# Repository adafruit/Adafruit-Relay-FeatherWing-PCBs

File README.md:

## Adafruit Relay FeatherWing PCBs
&nbsp; <br />
Click to purchase from the Adafruit Shop:
- [Latching Mini Relay FeatherWing](https://www.adafruit.com/product/2923)
- [Non-Latching Mini Relay FeatherWing](https://www.adafruit.com/product/2895)

The are two 'flavors' of these FeatherWings, one is the Latching relay, requires two pins, a SET and UNSET and instead of keeping the SET pin high, you only have to pulse each pin high for 10ms to latch the relay open or closed. You need two pins but save power. Note, if power is lost, the relay will stay in the last setting.

The other type of relay FeatherWing is the simple Non-Latching relay, it requires only a single signal pin.

Both FeatherWings use the same family of relay. You can switch up to 2A of resistive current at 30VDC or ~40VAC or lower. At 110VDC you can switch up to 0.3A, at 120VAC up to 0.5A, and at 250VAC you can switch up to 0.6A. Check the datasheet for the relay for the exact switching capacity, and of course, for reactive/inductive loads you will need to derate. This isn't a relay you can use to turn on and off your washer/dryer, stick to 60W or less. For up to 1200W devices, check out our Power Featherwing which can handle up to 10A!

For more details, check out the product pages at
- https://www.adafruit.com/products/2923
- https://www.adafruit.com/products/2895

This is the PCB files for the Adafruit Relay FeatherWings. The format is EagleCAD schematic and board layout

### License

Adafruit invests time and resources providing this open source design, please support Adafruit and open-source hardware by purchasing products from [Adafruit](https://www.adafruit.com)!

All text above must be included in any redistribution

Designed by Limor Fried/Ladyada for Adafruit Industries.
Creative Commons Attribution/Share-Alike, all text above must be included in any redistribution. 
See license.txt for additional information.

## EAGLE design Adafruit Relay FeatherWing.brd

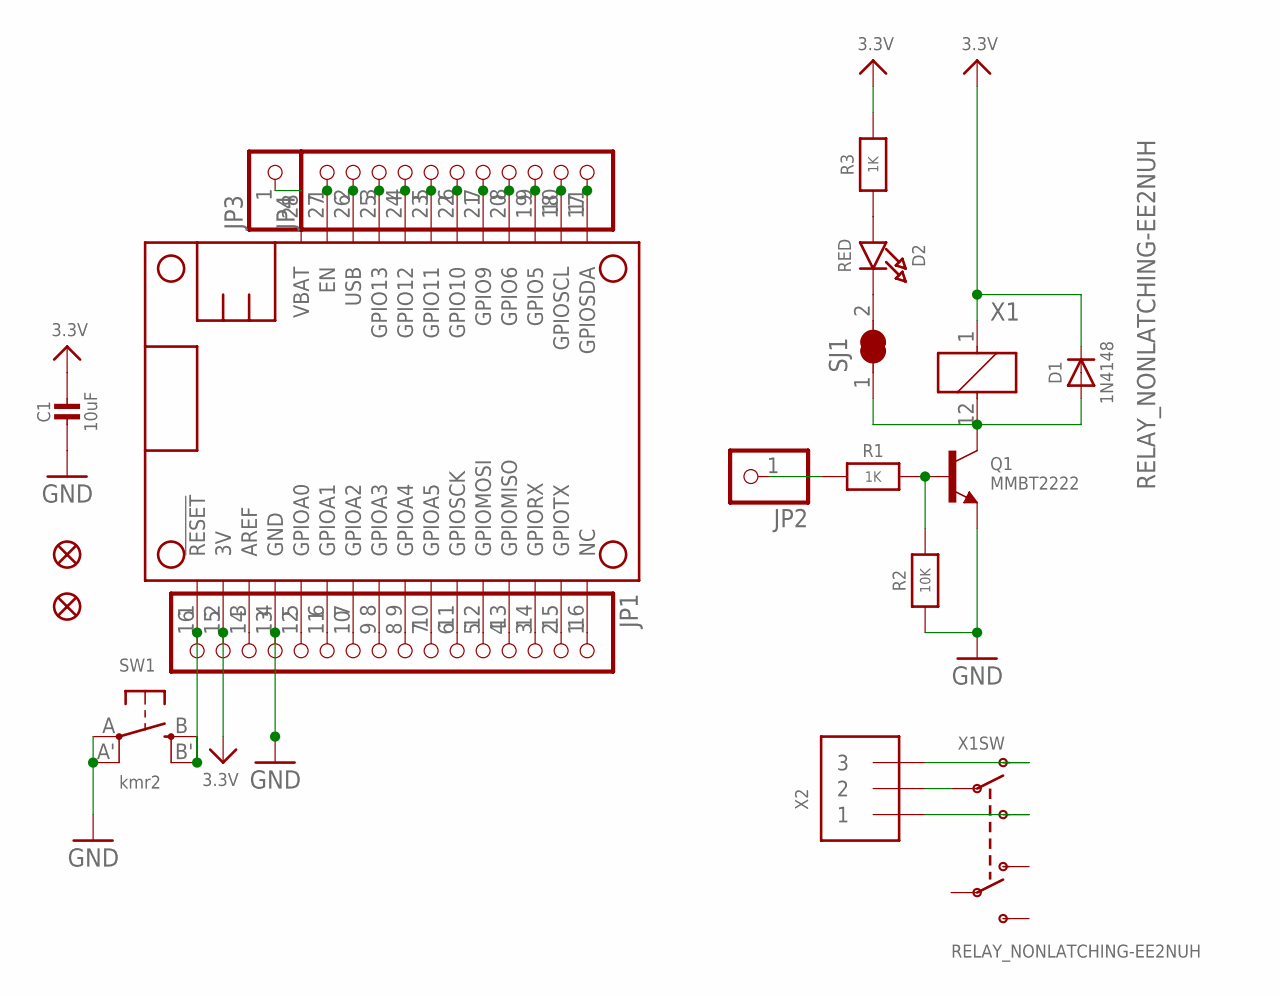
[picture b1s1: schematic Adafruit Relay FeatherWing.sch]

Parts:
C1: 10uF; 0805-NO
D1: 1N4148; SOD-323
D2: RED; CHIPLED_0805_NOOUTLINE
FID2, FID3: FIDUCIAL""; FIDUCIAL_1MM
JP1: HEADER-1X16ROUND; 1X16_ROUND
JP2, JP3: HEADER-1X1ROUND; 1X01_ROUND
JP4: HEADER-1X11; 1X11_ROUND
MS1: MICROSHIELD
Q1: MMBT2222; SOT23-R
R1, R3: 1K; 0805-NO
R2: 10K; 0805-NO
SJ1: SOLDERJUMPER_CLOSED; SOLDERJUMPER_CLOSEDWIRE
SW1: kmr2; BTN_KMR2_4.6X2.8
X1: RELAY_NONLATCHING-EE2NUH; RELAY_EE2_NOLATCH
X2: TERMBLOCK_1X3; TERMBLOCK_1X3-3.5MM

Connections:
3.3V: C1.1, D1.C, JP1.15, MS1.2 (3V), R3.2, X1.1
COM1: X1.9 (P1), X2.2
GND: C1.2, JP1.13, MS1.4 (GND), Q1.2 (E), R2.1, SW1.A, SW1.A' (P1)
unnamed: D1.A, Q1.3 (C), SJ1.1, X1.12 (2)
unnamed: JP1.1, MS1.16 (NC)
unnamed: JP1.2, MS1.15 (GPIOTX)
unnamed: JP1.3, MS1.14 (GPIORX)
unnamed: JP1.4, MS1.13 (GPIOMISO)
unnamed: JP1.5, MS1.12 (GPIOMOSI)
unnamed: JP1.6, MS1.11 (GPIOSCK)
unnamed: JP1.7, MS1.10 (GPIOA5)
unnamed: JP1.8, MS1.9 (GPIOA4)
unnamed: JP1.9, MS1.8 (GPIOA3)
unnamed: JP1.10, MS1.7 (GPIOA2)
unnamed: JP1.11, MS1.6 (GPIOA1)
unnamed: JP1.12, MS1.5 (GPIOA0)
unnamed: JP4.1, MS1.27 (EN)
unnamed: JP4.3, MS1.25 (GPIO13)
unnamed: JP4.4, MS1.24 (GPIO12)
unnamed: JP4.5, MS1.23 (GPIO11)
unnamed: JP4.6, MS1.22 (GPIO10)
unnamed: JP4.7, MS1.21 (GPIO9)
unnamed: JP4.8, MS1.20 (GPIO6)
unnamed: JP4.9, MS1.19 (GPIO5)
unnamed: Q1.1 (B), R1.2, R2.2
unnamed: JP1.14, MS1.3 (AREF)
unnamed: JP2.1, R1.1
unnamed: D2.C, SJ1.2
unnamed: D2.A, R3.1
unnamed: X1.10 (O1), X2.3
NO1: X1.8 (S1), X2.1
RESET: JP1.16, MS1.1 (!RESET), SW1.B (S), SW1.B' (S1)
SCL: JP4.10, MS1.18 (GPIOSCL)
SDA: JP4.11, MS1.17 (GPIOSDA)
USB: JP4.2, MS1.26 (USB)
VBAT: JP3.1, MS1.28 (VBAT)

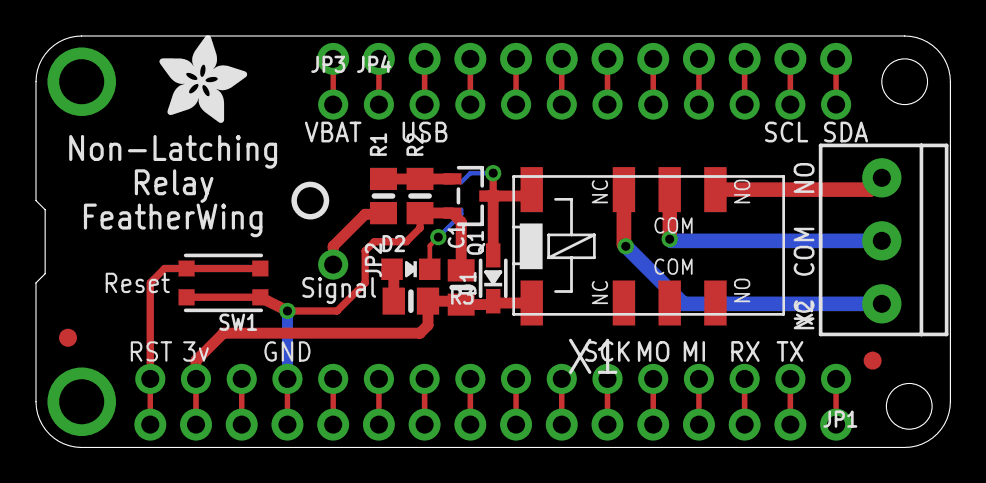
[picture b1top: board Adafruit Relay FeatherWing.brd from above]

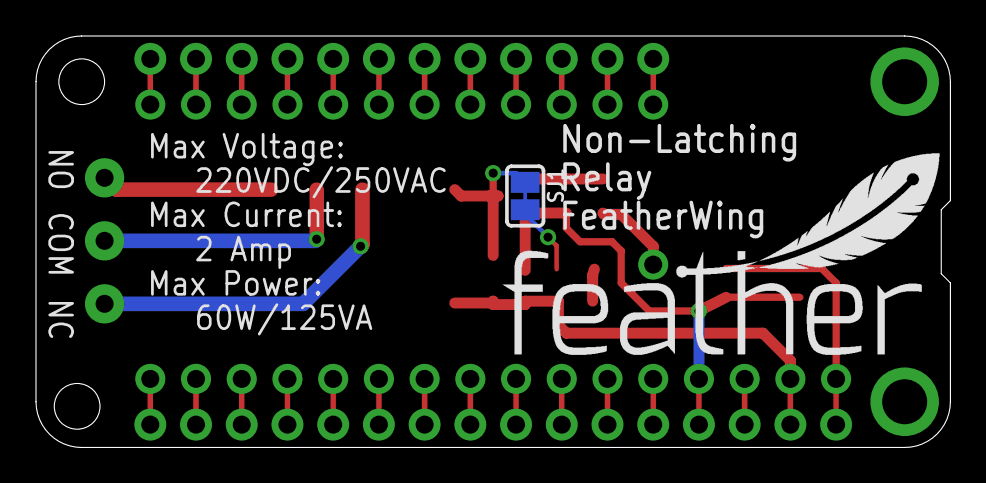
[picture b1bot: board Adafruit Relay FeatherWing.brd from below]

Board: 2 copper layers, 50.8 x 22.9 mm, 21 parts (2 on the bottom side), 36 nets.

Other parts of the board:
U$5: PCBFEAT-REV-040
U$6: FEATHERLOGO
U$7: ADAFRUIT_5MM

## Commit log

2016-06-21 init

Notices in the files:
parts and their libraries:
microbuilder: This work is placed in the public domain, and may be freely used for commercial and non-commercial work with the following conditions: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
